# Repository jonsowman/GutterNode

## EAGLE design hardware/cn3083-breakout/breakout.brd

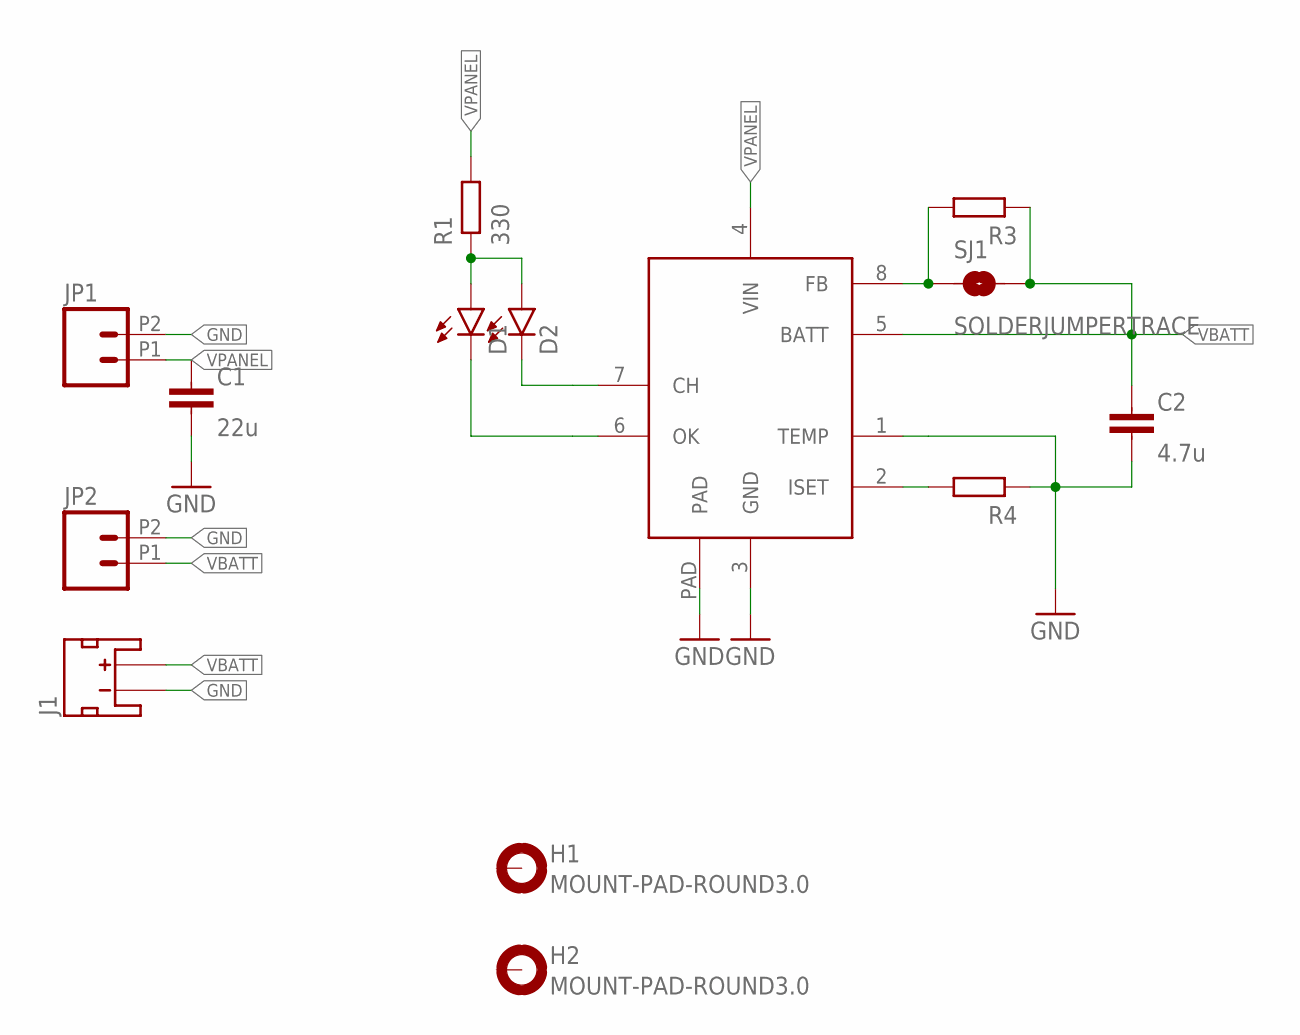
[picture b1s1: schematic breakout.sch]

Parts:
C1: 22u; C0603-N
C2: 4.7u; C0603-N
D1, D2: LED0603; LED-0603
H1, H2: MOUNT-PAD-ROUND3.0; 3,0-PAD
J1: JST_2MM_MALE_TH; JST-2-TH
JP1, JP2: M022.54MM_SCREWTERM; 1X02_2.54_SCREWTERM
R1: 330; R0603-N
R3, R4: RESISTOR0603-N; R0603-N
SJ1: SOLDERJUMPERTRACE; SJ_2S-TRACE
U1: CN3083; SO8-PAD

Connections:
GND: C1.2, C2.2, J1.2 (-), JP1.P2 (2), JP2.P2 (2), R4.1, U1.1 (TEMP), U1.3 (GND), U1.PAD
unnamed: D1.A, D2.A, R1.1
unnamed: R4.2, U1.2 (ISET)
unnamed: D2.C, U1.7 (CH)
unnamed: D1.C, U1.6 (OK)
unnamed: R3.2, SJ1.1, U1.8 (FB)
VBATT: C2.1, J1.1 (+), JP2.P1 (1), R3.1, SJ1.2, U1.5 (BATT)
VPANEL: C1.1, JP1.P1 (1), R1.2, U1.4 (VIN)

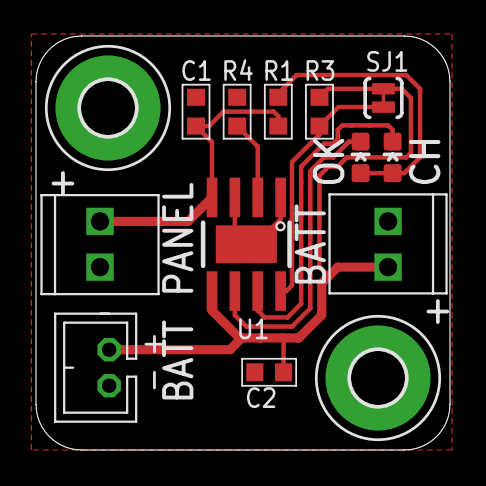
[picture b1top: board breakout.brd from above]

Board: 2 copper layers, 23.0 x 23.0 mm, 14 parts (0 on the bottom side), 8 nets.

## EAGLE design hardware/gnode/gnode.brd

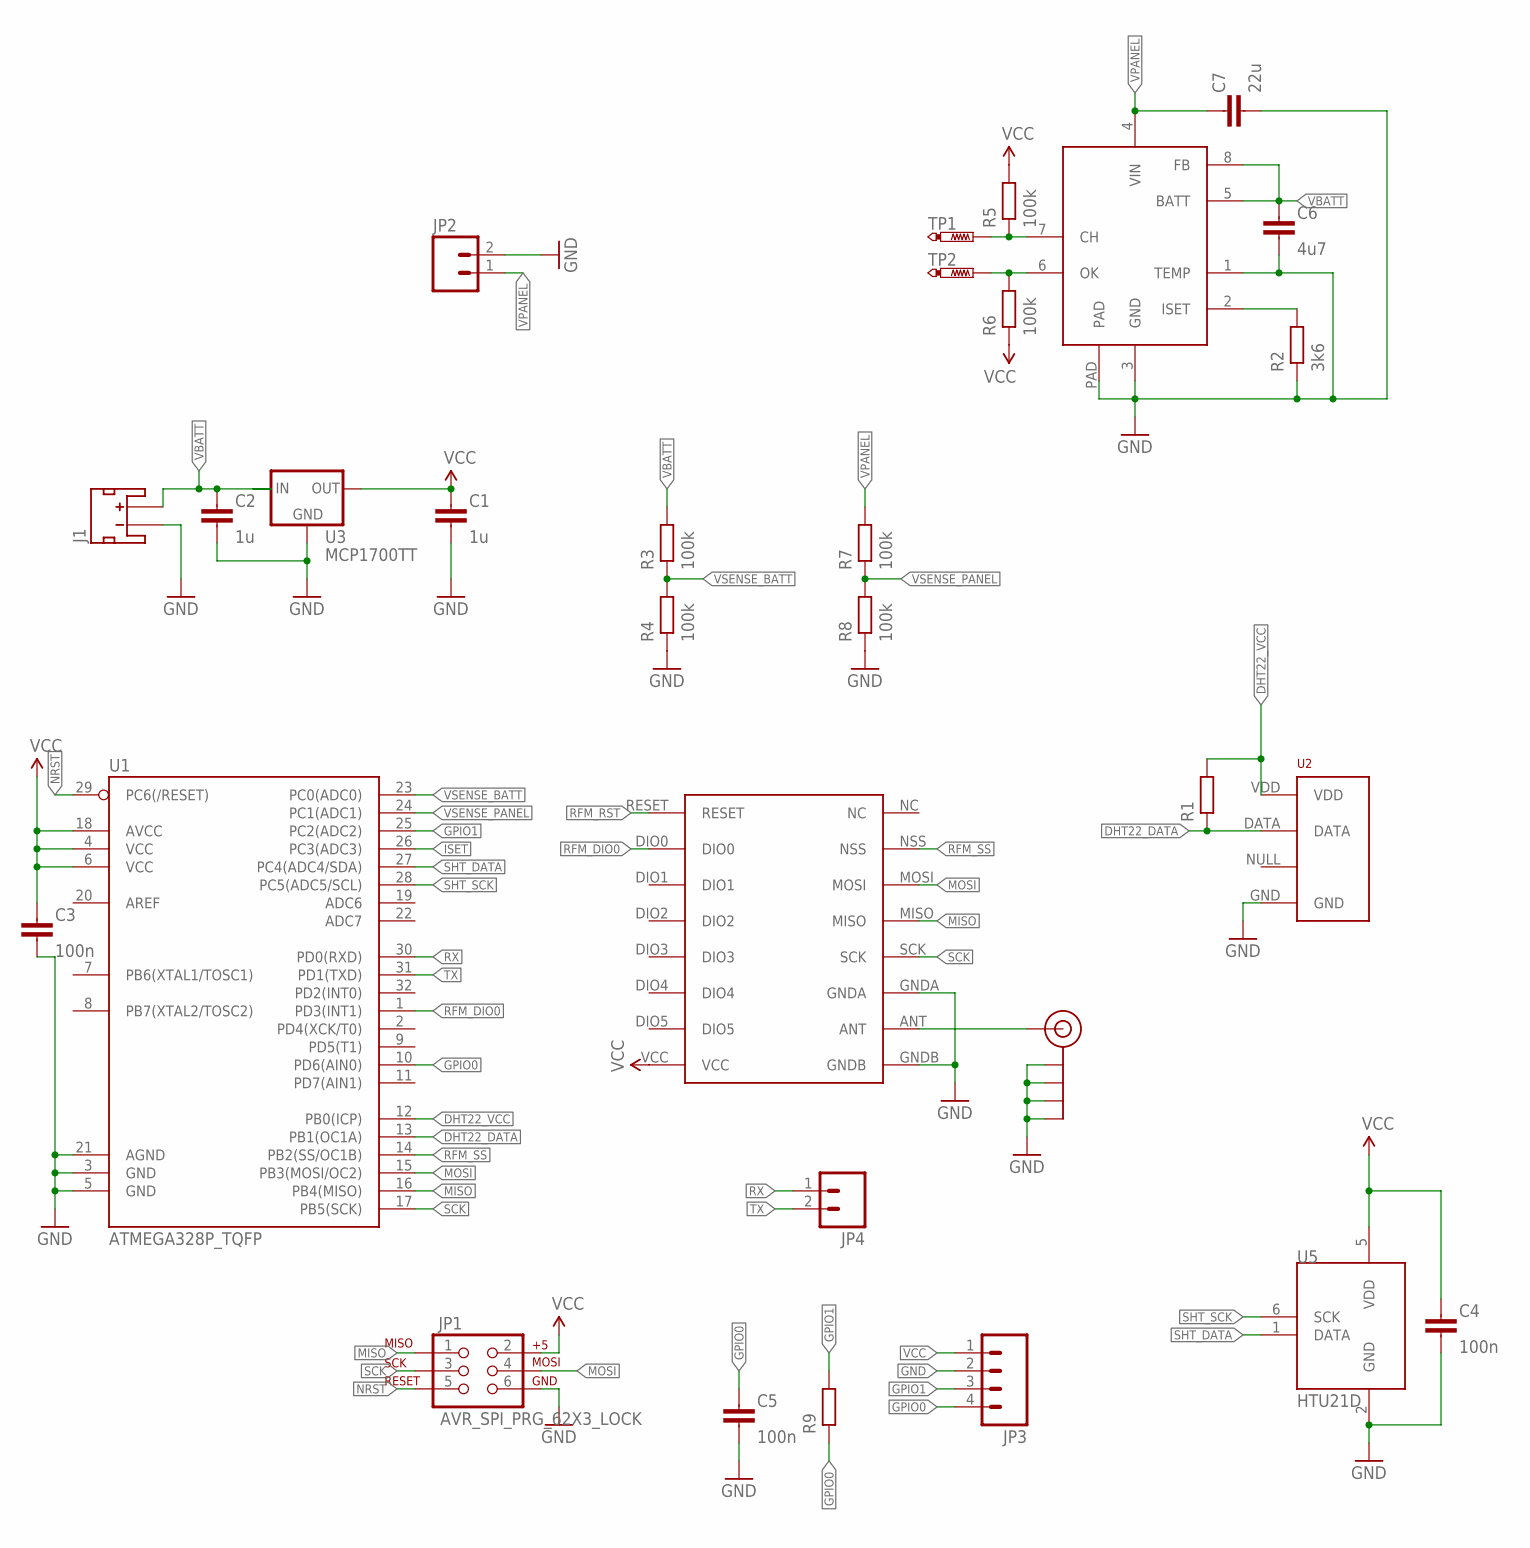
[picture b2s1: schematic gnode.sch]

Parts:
C1, C2: 1u; C0603-N
C3, C4, C5: 100n; C0603-N
C6: 4u7; C0603-N
C7: 22u; C0603-N
J1: JST_2MM_MALE_TH; JST-2-TH
J$1: SMA_EDGE; SMA-EDGE
JP1: AVR_SPI_PRG_62X3_LOCK; 2X3_LOCK
JP2, JP4: M02PTH; 1X02
JP3: M04PTH; 1X04
R1, R9: RESISTOR0603-N; R0603-N
R2: 3k6; R0603-N
R3, R4, R5, R6, R7, R8: 100k; R0603-N
TP1, TP2: PTR1B1,27; B1,27
U1: ATMEGA328P_TQFP; TQFP32-08
U2: RHT03_DHT-22_AM2302; RHT03_DHT-22
U3: MCP1700TT; SOT23
U4: CN3083; SO8-PAD
U5: HTU21D; DFN6-L
U$1: RFM69HW; RFM

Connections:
DHT22_DATA: R1.1, U1.13 (PB1(OC1A)), U2.DATA
DHT22_VCC: R1.2, U1.12 (PB0(ICP)), U2.VDD
GND: C1.2, C2.2, C3.2, C4.2, C5.2, C6.2, C7.2, J1.2 (-), J$1.GND@0 (GND), J$1.GND@1 (GND), J$1.GND@2 (GND), J$1.GND@3 (GND), JP1.6, JP2.2, JP3.2, R2.1, R4.1, R8.1, U1.3 (GND), U1.5 (GND), U1.21 (AGND), U2.GND, U3.1 (GND), U4.1 (TEMP), U4.3 (GND), U4.PAD, U5.2 (GND), U$1.GNDA, U$1.GNDB
GPIO0: C5.1, JP3.4, R9.1, U1.10 (PD6(AIN0))
GPIO1: JP3.3, R9.2, U1.25 (PC2(ADC2))
ISET: R2.2, U1.26 (PC3(ADC3)), U4.2 (ISET)
MISO: JP1.1, U1.16 (PB4(MISO)), U$1.MISO
MOSI: JP1.4, U1.15 (PB3(MOSI/OC2)), U$1.MOSI
unnamed: J$1.SIG (SIGNAL), U$1.ANT
unnamed: R5.1, TP1.TP, U4.7 (CH)
unnamed: R6.2, TP2.TP, U4.6 (OK)
NRST: JP1.5, U1.29 (PC6(/RESET))
RFM_DIO0: U1.1 (PD3(INT1)), U$1.DIO0
RFM_RST: U$1.RESET
RFM_SS: U1.14 (PB2(SS/OC1B)), U$1.NSS
RX: JP4.1, U1.30 (PD0(RXD))
SCK: JP1.3, U1.17 (PB5(SCK)), U$1.SCK
SHT_DATA: U1.27 (PC4(ADC4/SDA)), U5.1 (DATA)
SHT_SCK: U1.28 (PC5(ADC5/SCL)), U5.6 (SCK)
TX: JP4.2, U1.31 (PD1(TXD))
VBATT: C2.1, C6.1, J1.1 (+), R3.2, U3.3 (IN), U4.5 (BATT), U4.8 (FB)
VCC: C1.1, C3.1, C4.1, JP1.2, JP3.1, R5.2, R6.1, U1.4 (VCC), U1.6 (VCC), U1.18 (AVCC), U3.2 (OUT), U5.5 (VDD), U$1.VCC
VPANEL: C7.1, JP2.1, R7.2, U4.4 (VIN)
VSENSE_BATT: R3.1, R4.2, U1.23 (PC0(ADC0))
VSENSE_PANEL: R7.1, R8.2, U1.24 (PC1(ADC1))

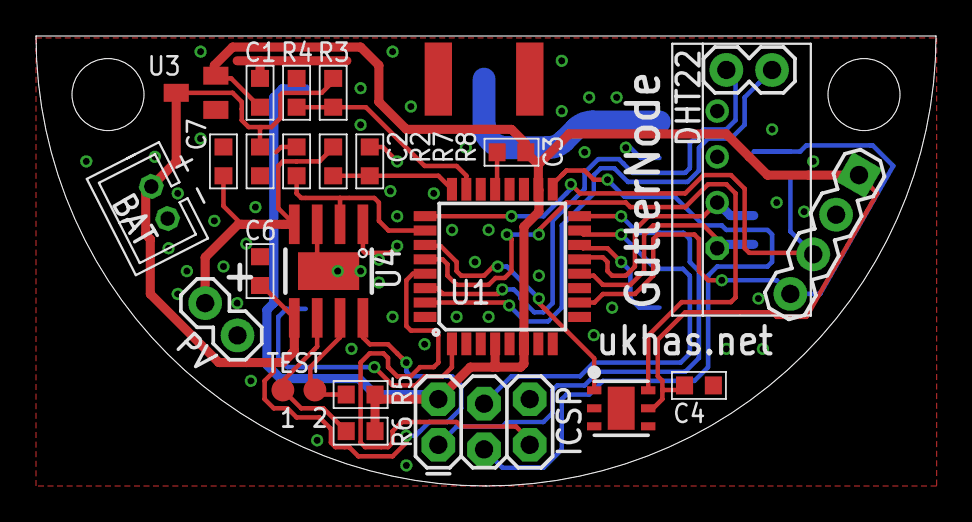
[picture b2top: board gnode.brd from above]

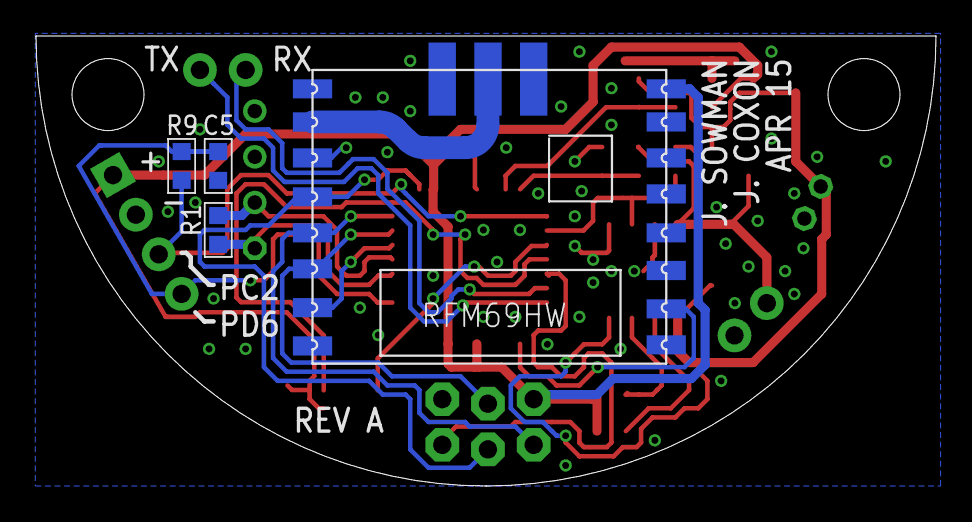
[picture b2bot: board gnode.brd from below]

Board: 2 copper layers, 50.0 x 25.0 mm, 30 parts (5 on the bottom side), 24 nets.

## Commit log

2015-03-25 added scad files for parts
2015-03-25 increased size of gutter top as was too tight (and we want a bit of overhang), also increased size of screw hole radius as too small
2015-03-25 now all the screw holes are the same size
2015-03-25 added clips to attach the gutternode to the gutter
2015-03-25 added stl of gutter top
2015-03-25 increased width of clip size and also gap between box and clips as ends appear to have slight curve
2015-03-25 moved screw holes and clips closer into centre to avoid gutter edges
2015-03-25 rebuilt stl
2015-03-25 updated screw holes to same as gutter top
2015-03-26 moved screw holes to hopefully fit, also made the wall thickness thinner to save of material
2015-03-26 added side panel and lip
2015-03-26 improved lip,
2015-03-26 added gnode stl
2015-03-27 fixed the position of the screw holes by moving them 1mm (after finding a small difference with the last test print), also added modules for 'mainbox' and 'sidepanel' to allow easy selection of the c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
2015-03-28 latest
2015-03-28 added stl of gutside
2015-03-30 moved files to enclosure/
2015-03-30 added first run of pcb stuff
2015-03-30 reduced to r25mm, added htu21d and icsp header
2015-03-30 switched to mcp1700
2015-03-30 added cn3083 solar charger
2015-03-30 sense panel and battery voltages
2015-03-30 centred the sma connector, placed resistors for sense potdivs
2015-04-02 routed
2015-04-02 tidying
2015-04-03 routed gpio for adc/pwm
2015-04-03 tidying. ready to go
2015-04-04 added RC for rain sensing. part numbers on silk
2015-04-04 ISET connected to ADC pin so we can calculate the charge current
2015-04-04 increased text size
2015-04-04 OCD improvements
2015-04-04 uart broken out
2015-04-04 bottom pad and heatsinking for cn3083
2015-04-05 cn3083 breakout
2015-04-05 git ignore eagle temp files
2015-04-05 improved ground return
2015-04-05 added caps for cn3083, oops
2015-04-05 added silk for name and revision
2015-04-07 final bits before manufacture

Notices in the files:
parts and their libraries:
SparkFun-Connectors: Licensing: Creative Commons ShareAlike 4.0 International - https://creativecommons.org/licenses/by-sa/4.0
